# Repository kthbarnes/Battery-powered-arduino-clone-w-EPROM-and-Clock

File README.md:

# Battery-powered-arduino-clone-w-EPROM-and-Clock

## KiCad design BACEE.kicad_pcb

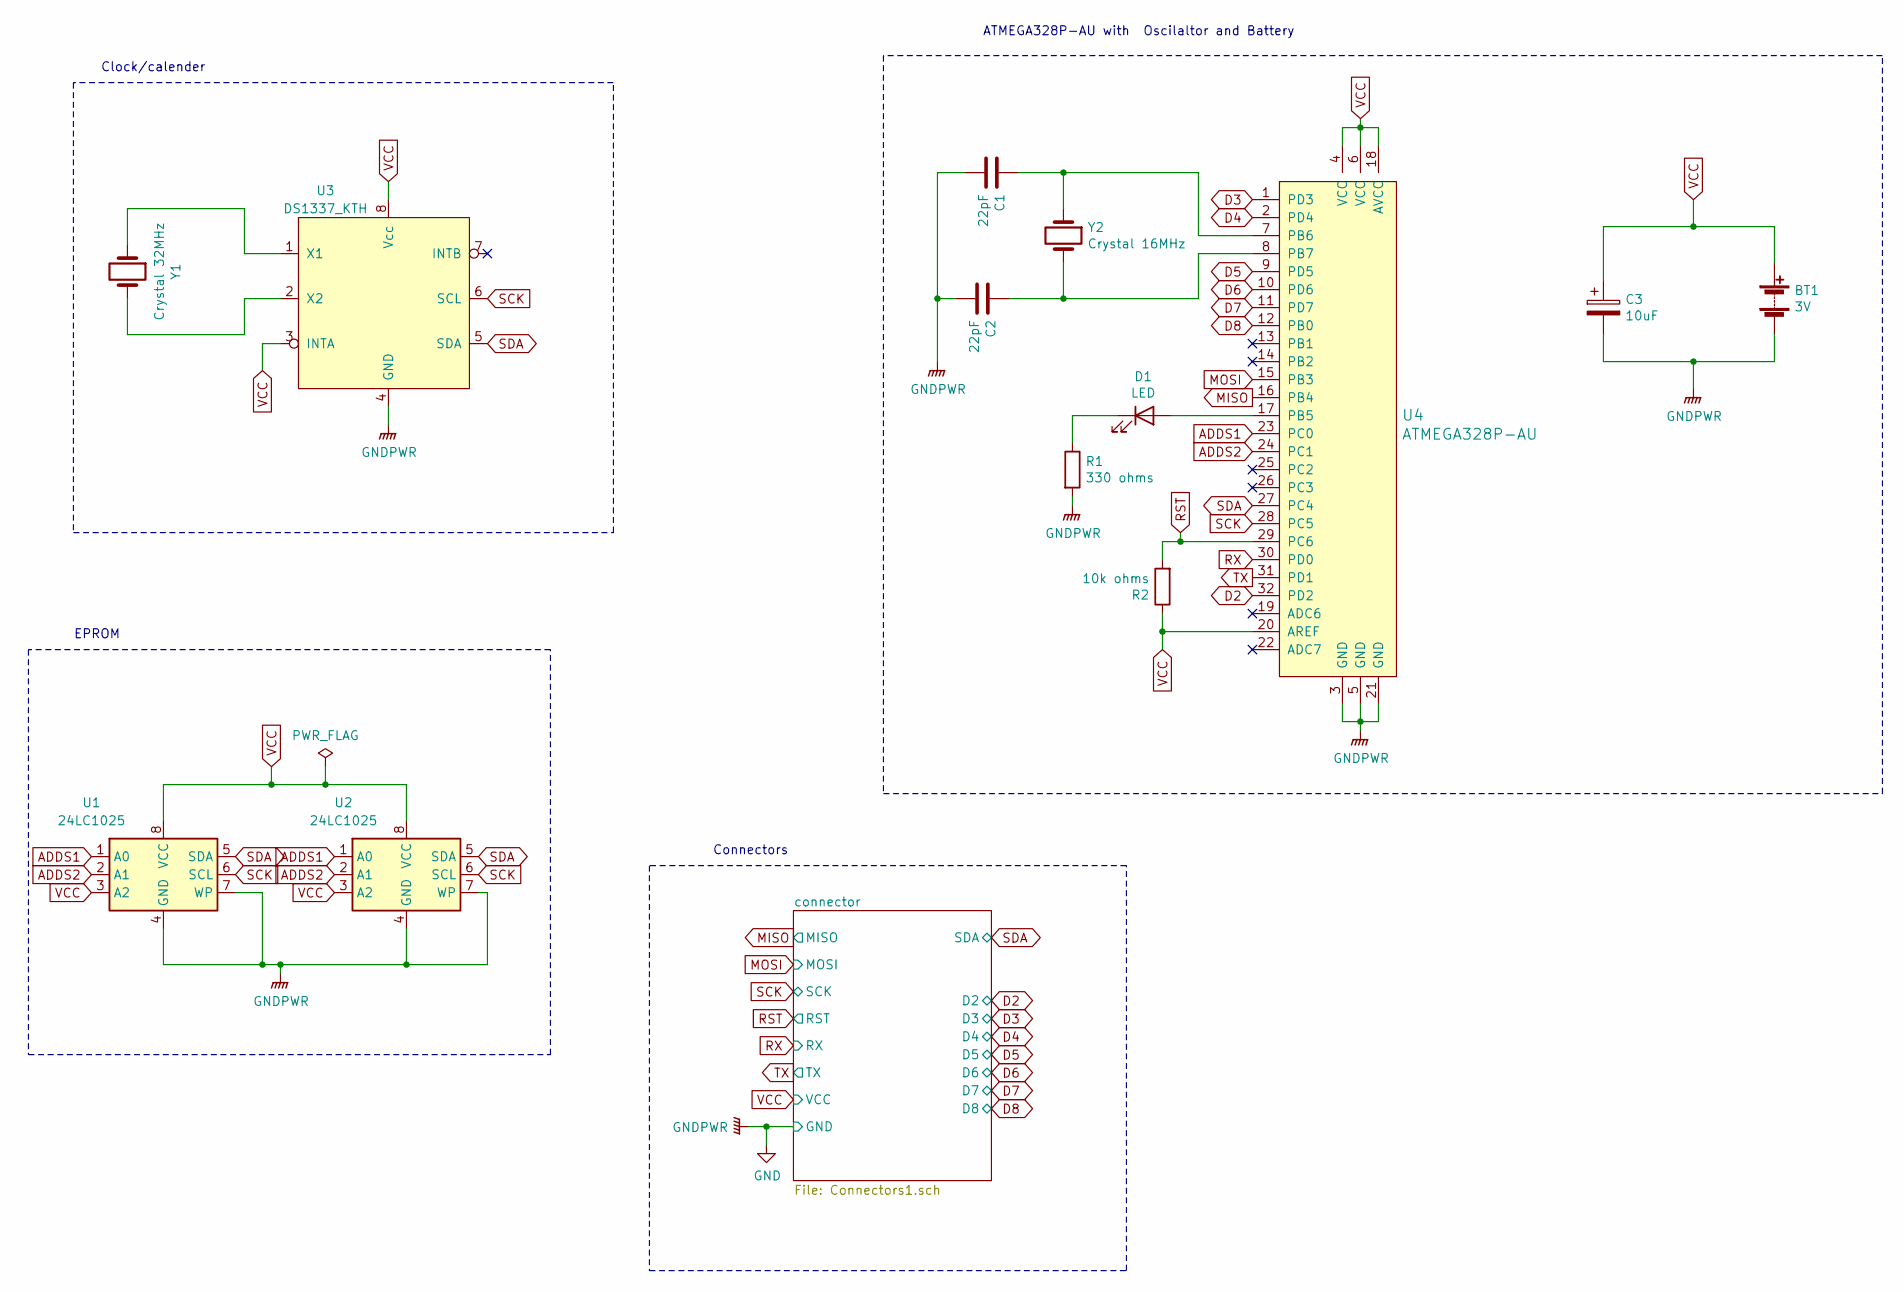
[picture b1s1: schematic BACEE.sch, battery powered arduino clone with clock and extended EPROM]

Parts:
BT1: 3V; PinHeader_1x02_P2.54mm_Vertical
C1, C2: 22pF; C_0805_2012Metric_Pad1.15x1.40mm_HandSolder
C3: 10uF; C_0805_2012Metric_Pad1.15x1.40mm_HandSolder
D1: LED; LED_0805_2012Metric_Pad1.15x1.40mm_HandSolder
R1: 330 ohms; R_0805_2012Metric_Pad1.15x1.40mm_HandSolder
R2: 10k ohms; R_0805_2012Metric_Pad1.15x1.40mm_HandSolder
U1, U2: 24LC1025; SOIJ-8_5.3x5.3mm_P1.27mm
U3: DS1337_KTH; SO-8_5.3x6.2mm_P1.27mm
U4: ATMEGA328P-AU; TQFP-32_7x7mm; MPN ATMEGA328P-AU; Digi-Key_PN ATMEGA328P-AU-ND
Y1: Crystal 32MHz; Crystal_SMD_MicroCrystal_CC7V-T1A-2Pin_3.2x1.5mm
Y2: Crystal 16MHz; Crystal_SMD_5032-2Pin_5.0x3.2mm_HandSoldering

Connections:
ADDS1: U1.1 (A0), U2.1 (A0), U4.23 (PC0)
ADDS2: U1.2 (A1), U2.2 (A1), U4.24 (PC1)
D2: U4.32 (PD2); also elsewhere on the board
D3: U4.1 (PD3); also elsewhere on the board
D4: U4.2 (PD4); also elsewhere on the board
D5: U4.9 (PD5); also elsewhere on the board
D6: U4.10 (PD6); also elsewhere on the board
D7: U4.11 (PD7); also elsewhere on the board
D8: U4.12 (PB0); also elsewhere on the board
GND: BT1.2 (-), C1.2, C2.2, C3.2, R1.2, U1.4 (GND), U1.7 (WP), U2.4 (GND), U2.7 (WP), U3.4 (GND), U4.3 (GND), U4.5 (GND), U4.21 (GND); also elsewhere on the board
MISO: U4.16 (PB4); also elsewhere on the board
MOSI: U4.15 (PB3); also elsewhere on the board
unnamed: C1.1, U4.7 (PB6), Y2.1
unnamed: C2.1, U4.8 (PB7), Y2.2
unnamed: D1.1 (K), R1.1
unnamed: D1.2 (A), U4.17 (PB5)
unnamed: U3.1 (X1), Y1.1
unnamed: U3.2 (X2), Y1.2
RST: R2.2, U4.29 (PC6); also elsewhere on the board
RX: U4.30 (PD0); also elsewhere on the board
SCK: U1.6 (SCL), U2.6 (SCL), U3.6 (SCL), U4.28 (PC5); also elsewhere on the board
SDA: U1.5 (SDA), U2.5 (SDA), U3.5 (SDA), U4.27 (PC4); also elsewhere on the board
TX: U4.31 (PD1); also elsewhere on the board
VCC: BT1.1 (+), C3.1, R2.1, U1.3 (A2), U1.8 (VCC), U2.3 (A2), U2.8 (VCC), U3.3 (INTA), U3.8 (Vcc), U4.4 (VCC), U4.6 (VCC), U4.18 (AVCC), U4.20 (AREF); also elsewhere on the board

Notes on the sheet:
Clock/calender
EPROM
ATMEGA328P-AU with Oscilaltor and Battery
Connectors

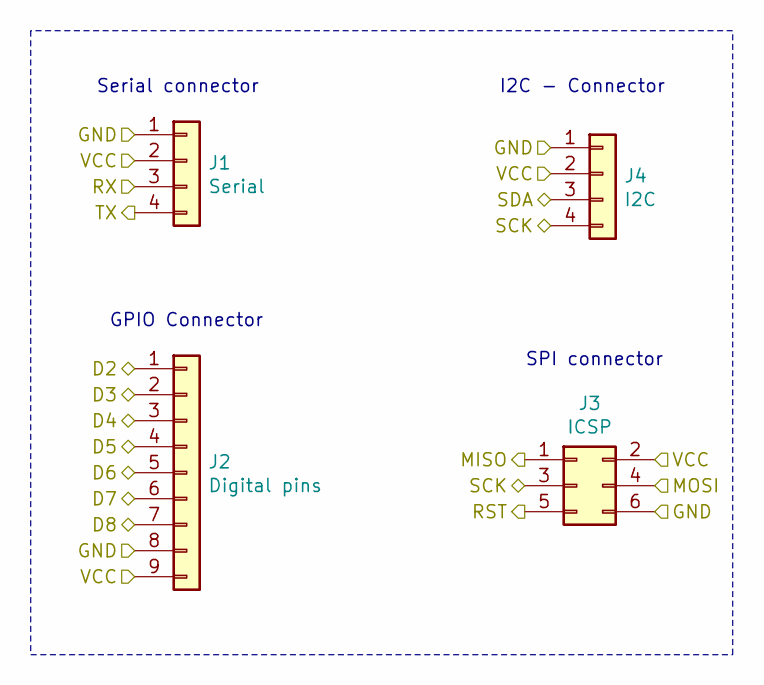
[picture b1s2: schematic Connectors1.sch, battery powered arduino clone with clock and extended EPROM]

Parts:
J1: Serial; PinHeader_1x04_P2.54mm_Vertical
J2: Digital pins; PinHeader_1x09_P2.54mm_Vertical
J3: ICSP; PinHeader_2x03_P2.54mm_Vertical
J4: I2C; PinHeader_1x04_P2.54mm_Vertical

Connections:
D2: J2.1; also elsewhere on the board
D3: J2.2; also elsewhere on the board
D4: J2.3; also elsewhere on the board
D5: J2.4; also elsewhere on the board
D6: J2.5; also elsewhere on the board
D7: J2.6; also elsewhere on the board
D8: J2.7; also elsewhere on the board
GND: J1.1, J2.8, J3.6, J4.1; also elsewhere on the board
MISO: J3.1; also elsewhere on the board
MOSI: J3.4; also elsewhere on the board
RST: J3.5; also elsewhere on the board
RX: J1.3; also elsewhere on the board
SCK: J3.3, J4.4; also elsewhere on the board
SDA: J4.3; also elsewhere on the board
TX: J1.4; also elsewhere on the board
VCC: J1.2, J2.9, J3.2, J4.2; also elsewhere on the board

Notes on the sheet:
Serial connector
I2C - Connector
GPIO Connector
SPI connector

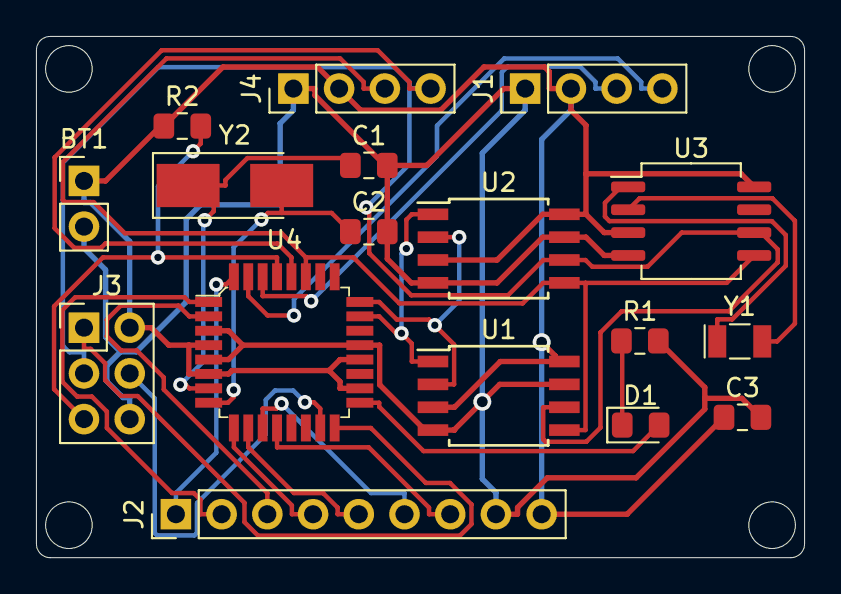
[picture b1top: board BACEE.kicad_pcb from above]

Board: 4 copper layers, 42.7 x 29.0 mm, 17 parts (0 on the bottom side), 24 nets.

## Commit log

2020-07-04 created a new symbol
2020-07-04 created files
2020-07-04 created hierarchial sheet
2020-07-04 wiring done ... no DRC errors
2020-07-04 placement and rounded outline
2020-07-04 arranged and annotated
2020-07-04 board layout with mounting holes
2020-07-04 comments and netlist
2020-07-04 routed using 4 layers
2020-07-04 silk screen added
2020-07-04 fully routed in 2 layers - saved a copy
